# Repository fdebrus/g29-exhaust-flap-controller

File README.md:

# G29 Exhaust Flap Controller

Open-source controller for the exhaust flap of the **BMW Z4 G29 M40i**: open the flap on demand
(even in Comfort mode) while keeping **full factory behaviour** the rest of the time.

Commercial kits exist, but the cheap ones replace the factory control entirely (their "AUTO" mode
does not hand control back to the car). This project fixes that with a fail-safe relay design.

## How it works

```
                       +------------------+
Engine computer (DME) -| NC              |
                       |   DPDT relay    COM|--- Exhaust flap actuator (signal wire)
ESP32-C3 PWM driver ---| NO              |
                       +------------------+
```

- **AUTO** (default, relay released): the car drives the flap exactly as from the factory.
- **ON / OFF**: the ESP32-C3 energizes the relay and sends its own PWM signal (flap open / closed).
- **Fail-safe**: if the board loses power, resets or crashes, the relay drops and the car is back in control.
- Only the **signal wire** is cut. The actuator's +12 V and ground stay on the original harness.
  The board takes its own power from a fused source in the trunk, not from the actuator wires.
- The relay's second pole connects a **dummy load** to the DME while the ESP32-C3 is in control,
  to try to avoid an open-circuit fault code.

Controls: the original 433 MHz key fob (ON / AUTO / OFF) and the kit's dashboard button, whose
cabin box also transmits on 433 MHz. Nothing is wired from the dashboard to the board.

## Hardware

Board **v3**: Seeed XIAO ESP32-C3 on socket strips, **on-board 433 MHz receiver** (JSMSEMI
SYN480R + 13.52127 MHz crystal, wire antenna pad), SMT passives (0603/0805, SMA, SOD-123,
SOT-23, DPAK), Omron G5V-2 DPDT relay, two 2-pin screw terminals. **58 x 40 mm**, 2 layers,
29 placed parts, designed for JLCPCB assembly (`hardware/v3-xiao-esp32c3/jlcpcb/`). No RXB6
module any more.

Earlier boards are in the git history only: v2 (same circuit with through-hole parts, an RXB6
module and a wired dashboard input, 60 x 46 mm) before the `v2-removed` tag, v1 (ESP32-DevKitC)
before the `v1-removed` tag.

## Project status

- [x] Teardown and analysis of the commercial kit ([docs/findings.md](docs/findings.md))
- [x] Firmware (AUTO / ON / OFF over 433 MHz: fob + dashboard button, fail-safe start)
- [x] PCB v3 (XIAO ESP32-C3, on-board SYN480R receiver, SMT, 58 x 40 mm, 3 mounting holes, DRC clean)
- [x] 3D-printed enclosure (OpenSCAD, 62.8 x 44.8 x 26 mm, not yet test-printed)
- [ ] Receiver sensitivity check against an RXB6 (first board)
- [x] Harness survey on the car: tap point and wire identification ([docs/harness.md](docs/harness.md))
- [ ] **Bench measurement of the kit's output signal** ([docs/measurement.md](docs/measurement.md))
- [ ] Measurement on the car (DME signal, actuator input impedance)
- [ ] Set PWM frequency / duty cycles in the firmware
- [ ] Verify XIAO footprint (1:1 print) and order the assembled PCB
- [ ] Assembly, bench test, installation ([docs/installation.md](docs/installation.md))
- [ ] Check fault memory after a few drives

## Repository layout

| Path                              | Content                                                      |
| --------------------------------- | ------------------------------------------------------------ |
| `firmware/g29_exhaust_flap_xiao/` | Firmware (Seeed XIAO ESP32-C3)                               |
| `hardware/v3-xiao-esp32c3/`       | KiCad board, Gerbers, previews, DRC report, JLCPCB BOM + CPL, 3D-printed enclosure |
| `tools/pcb-generator/`            | Scripts that regenerate the board (KiCad 7 + freerouting)    |
| `docs/`                           | Findings, harness survey, measurement, installation, shopping list |

## Important values still to confirm

The firmware PWM values are **placeholders** until measured:

| Parameter         | Current value | Source                                   |
| ----------------- | ------------- | ---------------------------------------- |
| `PWM_FREQ_HZ`     | 100           | guess - **must be measured**             |
| `DUTY_OPEN_PCT`   | 95 %          | BMW F30 measurement, not verified on G29 |
| `DUTY_CLOSED_PCT` | 5 %           | BMW F30 measurement, not verified on G29 |

## Disclaimer

Personal project, provided as-is. Modifying the exhaust behaviour may affect road legality
(noise approval), the vehicle inspection, warranty and insurance. The DME may log fault codes while
the controller is in ON/OFF mode. Measure before connecting anything to the car. Use at your own risk.

## License

MIT - see [LICENSE](LICENSE).

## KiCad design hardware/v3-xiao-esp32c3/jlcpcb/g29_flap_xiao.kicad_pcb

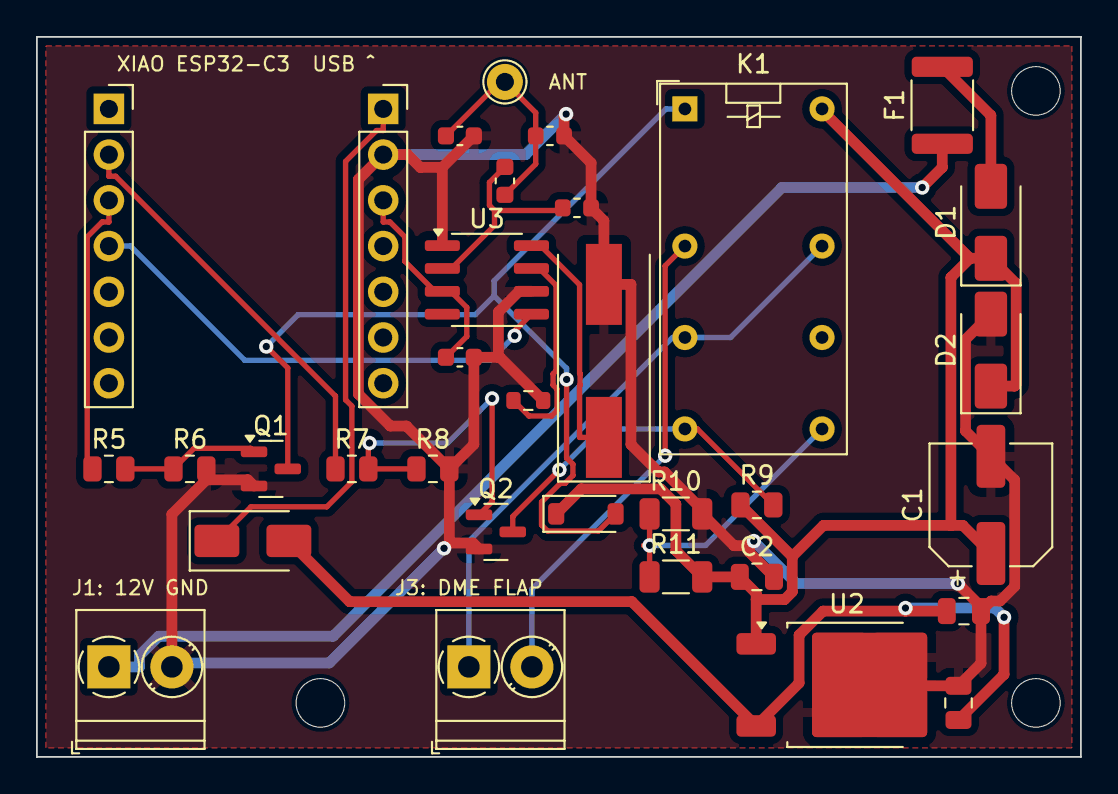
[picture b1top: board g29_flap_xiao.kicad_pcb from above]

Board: 2 copper layers, 58.0 x 40.0 mm, 36 parts (0 on the bottom side), 21 nets.

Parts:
ANT1: ANT 17cm; TestPoint_THTPad_D2.0mm_Drill1.0mm
C1: 100u 35V; CP_Elec_6.3x7.7
C2, C3: 100n; C_0805_2012Metric
C4: 10u; C_0805_2012Metric
C7: 1.8p C0G; C_0603_1608Metric
C8: 6.8p C0G; C_0603_1608Metric
C9: 1u; C_0603_1608Metric
D1, D6: SS14; D_SMA
D2: SMAJ20A; D_SMA
D5: 1N4148W; D_SOD-123
F1: PTC 0.5A; Fuse_1812_4532Metric
H1, H2, H3: M2.5
J1: PWR; TerminalBlock_Phoenix_PT-1,5-2-3.5-H_1x02_P3.50mm_Horizontal
J3: FLAP; TerminalBlock_Phoenix_PT-1,5-2-3.5-H_1x02_P3.50mm_Horizontal
K1: G5V-2-H1 DC12; Relay_DPDT_Omron_G5V-2
L1: 27nH; L_0603_1608Metric
L2: 47nH; L_0603_1608Metric
Q1, Q2: S8050; SOT-23
R5, R7: 1k; R_0805_2012Metric
R6, R8: 100k; R_0805_2012Metric
R9: 1k opt; R_0805_2012Metric
R10: DUM-GND; R_1206_3216Metric
R11: DUM-12V; R_1206_3216Metric
R12: 0R; R_0603_1608Metric
U1A: XIAO left; PinSocket_1x07_P2.54mm_Vertical
U1B: XIAO right; PinSocket_1x07_P2.54mm_Vertical
U2: 78M05; TO-252-2
U3: SYN480R; SOIC-8_3.9x4.9mm_P1.27mm
Y1: 13.52127MHz; Crystal_SMD_HC49-SD

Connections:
+3V3: C9.1, U1B.3, U3.3
+5V: C3.1, C4.1, D6.2, U2.3
+5V_X: D6.1, U1B.1
+12V: C1.1, C2.1, D1.1, D2.1, D5.1, K1.16, R9.1, R11.2, U2.1
+12V_F: D1.2, F1.2
+12V_IN: F1.1, J1.1
ACT_SIG: J3.2, K1.4
ANT_IN: ANT1.1, C7.1, C8.1, L1.1
COIL_N: D5.2, K1.1, Q1.3
DME_SIG: J3.1, K1.6, K1.13
DUMMY: K1.9, R10.1, R11.1
GND: C1.2, C2.2, C3.2, C4.2, C7.2, C9.2, D2.2, J1.2, L1.2, L2.2, Q1.2, Q2.2, R6.2, R8.2, R10.2, R12.2, U1B.2, U2.2, U3.1, U3.6, Y1.2
IO3: R7.1, U1A.2
IO4: R5.1, U1A.3
IO5: U1A.4, U3.5
PWM_OUT: K1.8, Q2.3, R9.2
Q1_B: Q1.1, R5.2, R6.1
Q2_B: Q2.1, R7.2, R8.1
RF_IN: C8.2, L2.1, U3.2
SQ: R12.1, U3.7
XTAL: U3.8, Y1.1

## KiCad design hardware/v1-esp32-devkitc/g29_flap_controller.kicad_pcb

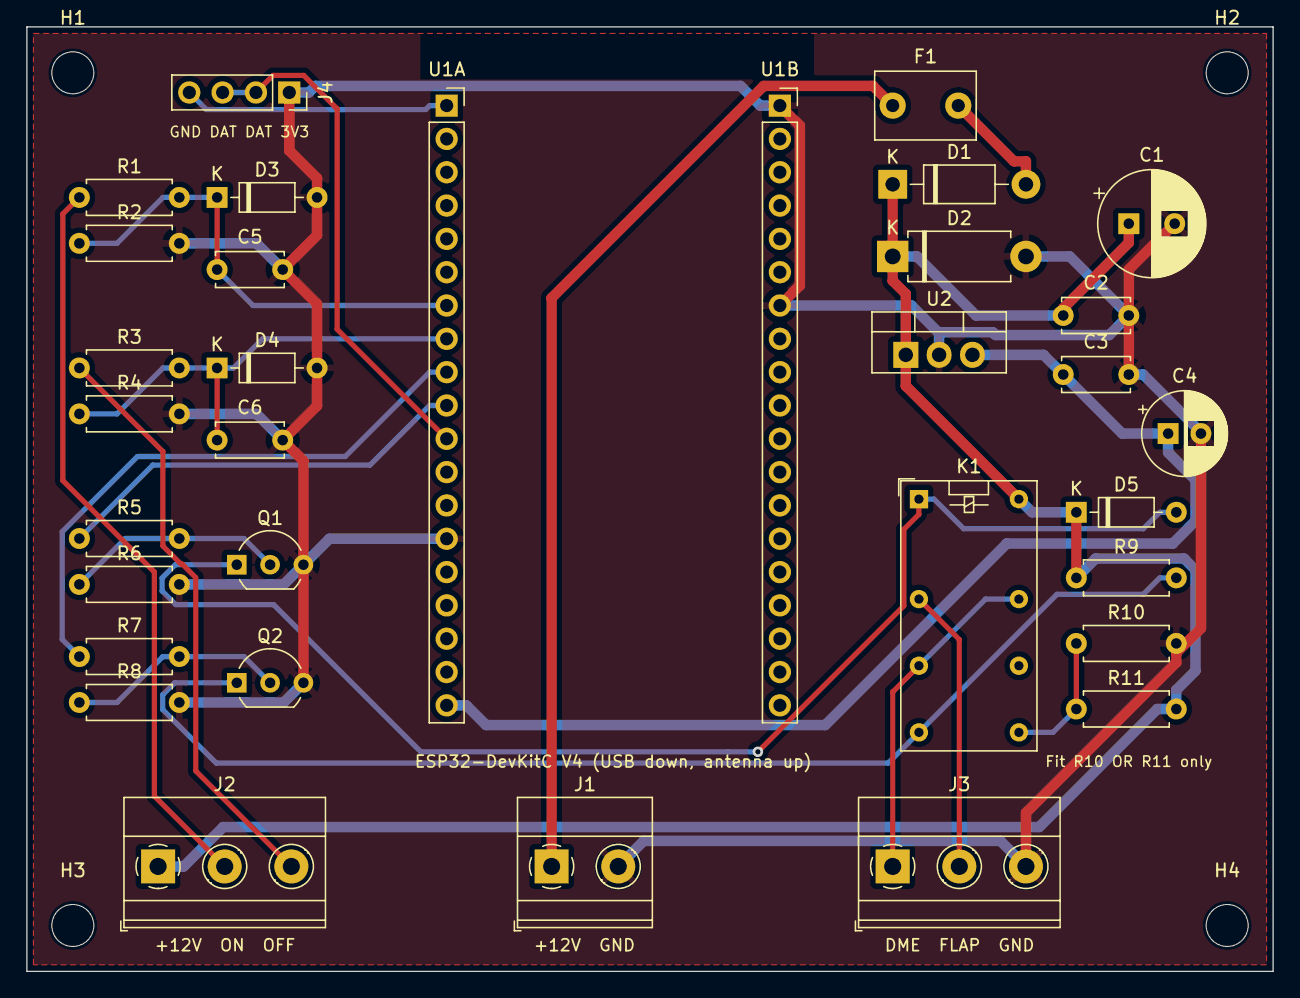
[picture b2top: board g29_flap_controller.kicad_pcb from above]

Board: 2 copper layers, 95.0 x 72.0 mm, 37 parts (0 on the bottom side), 20 nets.

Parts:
C1: 100u 35V; CP_Radial_D8.0mm_P3.50mm
C2: 330n; C_Disc_D5.0mm_W2.5mm_P5.00mm
C3, C5, C6: 100n; C_Disc_D5.0mm_W2.5mm_P5.00mm
C4: 10u; CP_Radial_D6.3mm_P2.50mm
D1: 1N5819; D_DO-41_SOD81_P10.16mm_Horizontal
D2: P6KE20A; D_DO-15_P10.16mm_Horizontal
D3, D4: BZX79-C3V3; D_DO-35_SOD27_P7.62mm_Horizontal
D5: 1N4148; D_DO-35_SOD27_P7.62mm_Horizontal
F1: PTC 0.5A 60V; C_Disc_D7.5mm_W5.0mm_P5.00mm
H1, H2, H3, H4: M3; MountingHole_3.2mm_M3
J1: POWER; TerminalBlock_Phoenix_MKDS-1,5-2-5.08_1x02_P5.08mm_Horizont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
J2: DASH; TerminalBlock_Phoenix_MKDS-1,5-3-5.08_1x03_P5.08mm_Horizont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
J3: FLAP; TerminalBlock_Phoenix_MKDS-1,5-3-5.08_1x03_P5.08mm_Horizont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
J4: RF RX; PinSocket_1x04_P2.54mm_Vertical
K1: G5V-2-12VDC; Relay_DPDT_Omron_G5V-2
Q1, Q2: BC337; TO-92_Inline_Wide
R1, R3: 10k; R_Axial_DIN0207_L6.3mm_D2.5mm_P7.62mm_Horizontal
R2, R4: 3k3; R_Axial_DIN0207_L6.3mm_D2.5mm_P7.62mm_Horizontal
R5, R7: 1k; R_Axial_DIN0207_L6.3mm_D2.5mm_P7.62mm_Horizontal
R6, R8: 100k; R_Axial_DIN0207_L6.3mm_D2.5mm_P7.62mm_Horizontal
R9: 1k (opt); R_Axial_DIN0207_L6.3mm_D2.5mm_P7.62mm_Horizontal
R10: DUMMY-GND; R_Axial_DIN0207_L6.3mm_D2.5mm_P7.62mm_Horizontal
R11: DUMMY-12V; R_Axial_DIN0207_L6.3mm_D2.5mm_P7.62mm_Horizontal
U1A: ESP32 left; PinSocket_1x19_P2.54mm_Vertical
U1B: ESP32 right; PinSocket_1x19_P2.54mm_Vertical
U2: L7805; TO-220-3_Vertical

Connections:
+3V3: J4.4, U1A.1
+5V: C3.1, C4.1, U1A.19, U2.3
+12V: C1.1, C2.1, D1.1, D2.1, D5.1, J2.1, K1.16, R9.1, R11.2, U2.1
+12V_F: D1.2, F1.2
+12V_IN: F1.1, J1.1
ACT_SIG: J3.2, K1.4
COIL_N: D5.2, K1.1, Q1.1
DASH_OFF: J2.3, R3.1
DASH_ON: J2.2, R1.1
DME_SIG: J3.1, K1.6, K1.13
DUMMY: K1.9, R10.1, R11.1
GND: C1.2, C2.2, C3.2, C4.2, C5.2, C6.2, D2.2, D3.2, D4.2, J1.2, J3.3, J4.1, Q1.3, Q2.3, R2.2, R4.2, R6.2, R8.2, R10.2, U1A.14, U1B.1, U1B.7, U2.2
IO25: R7.1, U1A.9
IO26: R5.1, U1A.10
IO27: J4.2, J4.3, U1A.11
IO32: C5.1, D3.1, R1.2, R2.1, U1A.7
IO33: C6.1, D4.1, R3.2, R4.1, U1A.8
PWM_OUT: K1.8, Q2.1, R9.2
Q1_B: Q1.2, R5.2, R6.1
Q2_B: Q2.2, R7.2, R8.1

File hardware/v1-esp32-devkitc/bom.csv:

Ref,Qty,Value,Part / example,Footprint,Notes
U1A U1B,2,1x19 female header,2.54 mm socket strip,PinSocket_1x19,For ESP32-DevKitC V4 (38-pin); rows 25.4 mm apart
J4,1,1x4 female header,2.54 mm socket strip,PinSocket_1x04,RXB6 receiver: GND DATA DATA VCC (check your module)
J1,1,2-pin screw terminal,Phoenix MKDS 1.5/2-5.08,5.08 mm,Power in: +12V after contact / GND
J2,1,3-pin screw terminal,Phoenix MKDS 1.5/3-5.08,5.08 mm,Dashboard: +12V out / ON / OFF
J3,1,3-pin screw terminal,Phoenix MKDS 1.5/3-5.08,5.08 mm,DME signal (from car) / FLAP signal (to actuator) / GND
F1,1,PTC 0.5 A 60 V,Bourns MF-R050,radial 5.1 mm,Resettable fuse
D1,1,1N5819,Schottky 1 A 40 V,DO-41,Reverse-polarity protection (stripe = +12V side)
D2,1,P6KE20A,TVS 600 W unidirectional,DO-15,Stripe toward +12V
D3 D4,2,BZX79-C3V3,Zener 3.3 V 0.5 W,DO-35,Input clamp (stripe toward GPIO)
D5,1,1N4148,Signal diode,DO-35,Relay flyback (stripe toward +12V)
U2,1,L7805,5 V linear regulator TO-220,TO-220 vertical,Feeds ESP32 5V pin
C1,1,100 uF 35 V,Electrolytic,D8 mm P3.5,Observe polarity
C2,1,330 nF,Ceramic 50 V,P5.0,Regulator input
C3 C5 C6,3,100 nF,Ceramic 50 V,P5.0,
C4,1,10 uF 25 V,Electrolytic,D6.3 mm P2.5,Observe polarity
R1 R3,2,10 k,1/4 W,P7.62,Input divider top
R2 R4,2,3.3 k,1/4 W,P7.62,Input divider bottom
R5 R7,2,1 k,1/4 W,P7.62,Transistor base
R6 R8,2,100 k,1/4 W,P7.62,Base pull-down (keeps relay off during boot)
R9,1,1 k (optional),1/4 W,P7.62,PWM pull-up to 12 V - fit only if measurement shows it is needed
R10 / R11,1,TBD,1/4 W,P7.62,Dummy load - fit ONE: R10 to GND or R11 to 12V (value = measured actuator input)
Q1 Q2,2,BC337,NPN TO-92 (C-B-E),TO-92 wide,Q1 relay coil / Q2 PWM driver
K1,1,G5V-2-12VDC,Omron DPDT signal relay,G5V-2,
-,1,ESP32-DevKitC V4,Espressif 38-pin,-,Measure row spacing before ordering
-,1,RXB6,433 or 315 MHz receiver,-,Match your remote's frequency
-,4,M3 standoffs,-,-,
